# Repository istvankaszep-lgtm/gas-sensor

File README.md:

# gas-sensor
I'm making this gas sensor, if it dedect's gas, the buzzer will go off and it will print a warning sign on the lcd desplay. it also print' s the temperature.

# how to uploade the code.
To upload the code (firmware) you need to download arduino ide, then download this three librarys from the IDE library:
1. LiquidCrystal_I2C (Frank de Brabander)
2. OneWire (Jim Studt / Paul Stoffregen)
3. DallasTemperature (Miles Burton)

4. then uploade the firmware from this repo, and uploade the code to the arduino nano.

5. # part's:
6. 1. lcd screen
   2. gas sensor
   3. arduino nano
   4. Temperature sensor
   5. buzzer
   6. rgb led
   7. usb_c port
  
   8.

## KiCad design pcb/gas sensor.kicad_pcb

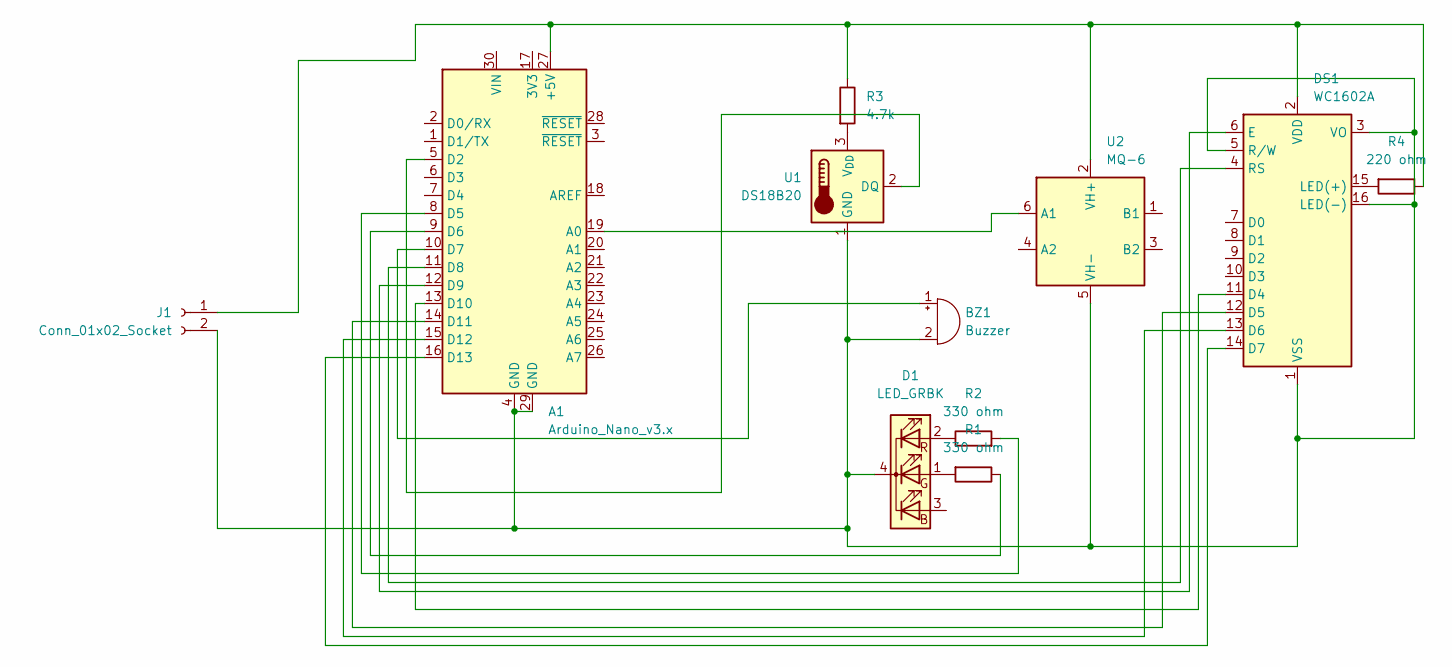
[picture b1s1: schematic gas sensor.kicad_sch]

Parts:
A1: Arduino_Nano_v3.x; Arduino_Nano
BZ1: Buzzer; Buzzer_12x9.5RM7.6
D1: LED_GRBK; LED_D5.0mm-4_RGB
DS1: WC1602A
J1: Conn_01x02_Socket; Altech_AK300_1x02_P5.00mm_45-Degree
R1, R2: 330 ohm; R_Axial_DIN0207_L6.3mm_D2.5mm_P10.16mm_Horizontal
R3: 4.7k; R_Axial_DIN0207_L6.3mm_D2.5mm_P10.16mm_Horizontal
R4: 220 ohm; R_Axial_DIN0207_L6.3mm_D2.5mm_P10.16mm_Horizontal
U1: DS18B20; TO-92_Inline
U2: MQ-6

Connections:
unnamed: A1.27 (+5V), DS1.2 (VDD), J1.1, R3.1, R4.1, U2.2 (VH+)
unnamed: A1.19 (A0), U2.6 (A1)
unnamed: A1.5 (D2), U1.2 (DQ)
unnamed: A1.8 (D5), R2.2
unnamed: A1.9 (D6), R1.1
unnamed: A1.10 (D7), BZ1.1 (+)
unnamed: A1.11 (D8), DS1.4 (RS)
unnamed: A1.12 (D9), DS1.6 (E)
unnamed: A1.13 (D10), DS1.11 (D4)
unnamed: A1.14 (D11), DS1.12 (D5)
unnamed: A1.15 (D12), DS1.13 (D6)
unnamed: A1.16 (D13), DS1.14 (D7)
unnamed: A1.4 (GND), A1.29 (GND), BZ1.2 (-), D1.4 (K), DS1.1 (VSS), DS1.3 (VO), DS1.5 (R/W), DS1.16 (LED(-)), J1.2, U1.1 (GND), U2.5 (VH-)
unnamed: D1.1 (GA), R1.2
unnamed: D1.2 (RA), R2.1
unnamed: DS1.15 (LED(+)), R4.2
unnamed: R3.2, U1.3 (V_{DD})

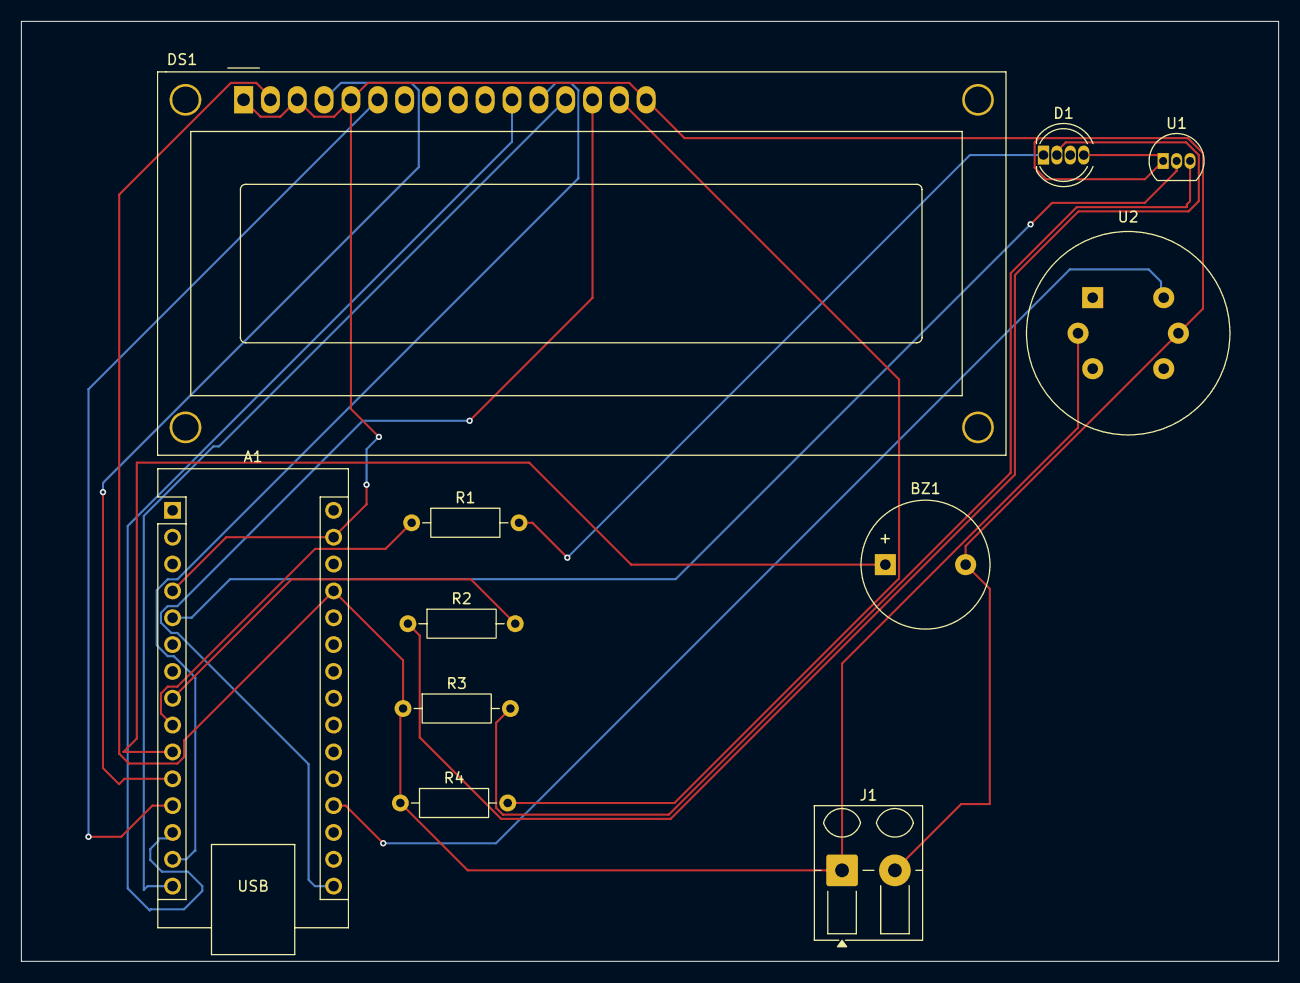
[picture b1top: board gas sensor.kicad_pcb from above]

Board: 2 copper layers, 119.0 x 89.0 mm, 11 parts (0 on the bottom side), 17 nets.
